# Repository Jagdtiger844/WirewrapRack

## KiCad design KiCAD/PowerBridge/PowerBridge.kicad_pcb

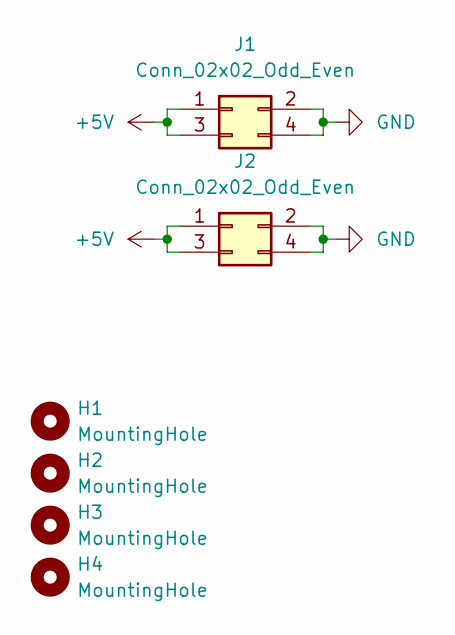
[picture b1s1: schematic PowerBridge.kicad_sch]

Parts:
H1, H2, H3, H4: MountingHole; MountingHole_2.2mm_M2
J1, J2: Conn_02x02_Odd_Even; PinSocket_2x02_P2.54mm_Vertical

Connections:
+5V: J1.1, J1.3, J2.1, J2.3
GND: J1.2, J1.4, J2.2, J2.4

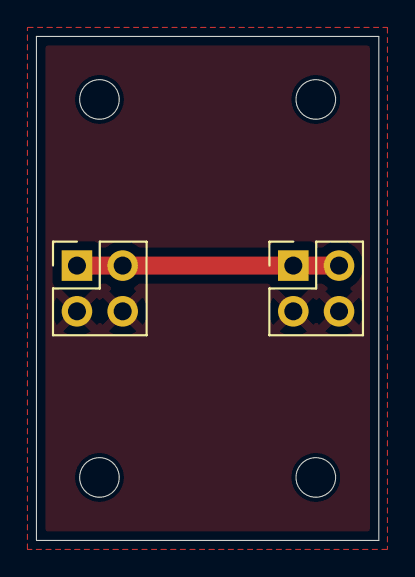
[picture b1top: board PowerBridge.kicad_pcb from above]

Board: 2 copper layers, 19.0 x 28.0 mm, 6 parts (0 on the bottom side), 2 nets.

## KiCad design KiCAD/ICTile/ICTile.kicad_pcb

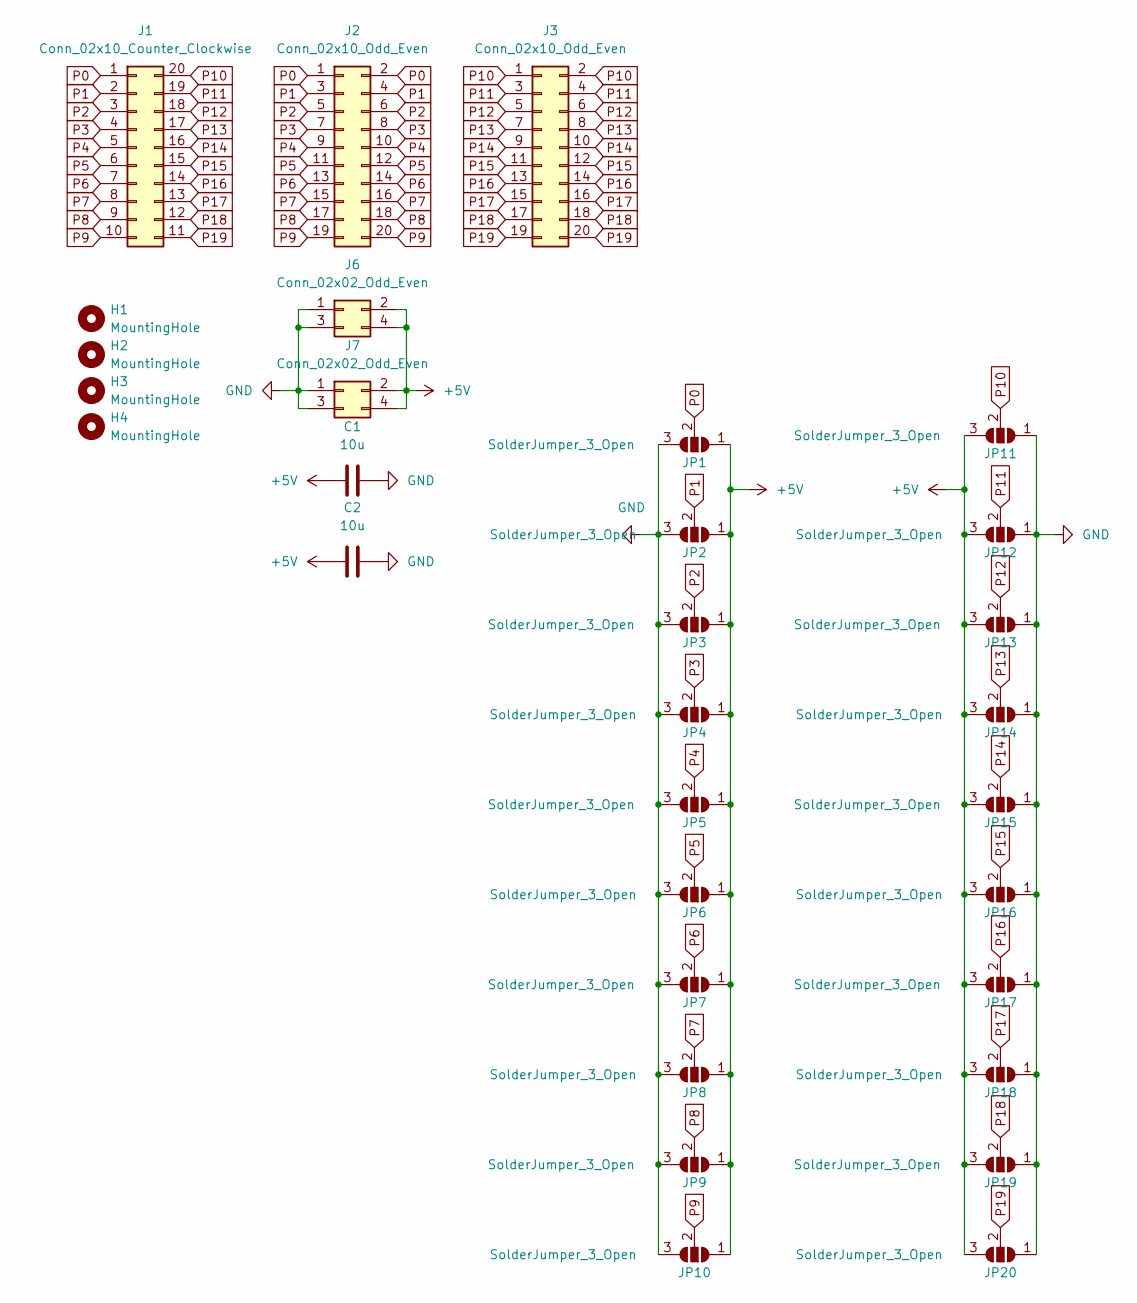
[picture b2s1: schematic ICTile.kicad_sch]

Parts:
C1, C2: 10u; C_1206_3216Metric_Pad1.33x1.80mm_HandSolder
H1, H2, H3, H4: MountingHole; MountingHole_2.2mm_M2
J1: Conn_02x10_Counter_Clockwise; DIP-20_W8.89mm_SMDSocket_LongPads
J2, J3: Conn_02x10_Odd_Even; PinHeader_2x10_P2.54mm_Vertical_SMD
J6, J7: Conn_02x02_Odd_Even; PinHeader_2x02_P2.54mm_Vertical_SMD
JP1, JP2, JP3, JP4, JP5, JP6, JP7, JP8, JP9, JP10, JP11, JP12, JP13, JP14, JP15, JP16, JP17, JP18, JP19, JP20: SolderJumper_3_Open; 1206_3Way_Open

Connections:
+5V: C1.1, C2.1, J6.2, J6.4, J7.2, J7.4, JP1.1 (A), JP2.1 (A), JP3.1 (A), JP4.1 (A), JP5.1 (A), JP6.1 (A), JP7.1 (A), JP8.1 (A), JP9.1 (A), JP10.1 (A), JP11.3 (B), JP12.3 (B), JP13.3 (B), JP14.3 (B), JP15.3 (B), JP16.3 (B), JP17.3 (B), JP18.3 (B), JP19.3 (B), JP20.3 (B)
GND: C1.2, C2.2, J6.1, J6.3, J7.1, J7.3, JP1.3 (B), JP2.3 (B), JP3.3 (B), JP4.3 (B), JP5.3 (B), JP6.3 (B), JP7.3 (B), JP8.3 (B), JP9.3 (B), JP10.3 (B), JP11.1 (A), JP12.1 (A), JP13.1 (A), JP14.1 (A), JP15.1 (A), JP16.1 (A), JP17.1 (A), JP18.1 (A), JP19.1 (A), JP20.1 (A)
P0: J1.1, J2.1, J2.2, JP1.2 (C)
P1: J1.2, J2.3, J2.4, JP2.2 (C)
P2: J1.3, J2.5, J2.6, JP3.2 (C)
P3: J1.4, J2.7, J2.8, JP4.2 (C)
P4: J1.5, J2.9, J2.10, JP5.2 (C)
P5: J1.6, J2.11, J2.12, JP6.2 (C)
P6: J1.7, J2.13, J2.14, JP7.2 (C)
P7: J1.8, J2.15, J2.16, JP8.2 (C)
P8: J1.9, J2.17, J2.18, JP9.2 (C)
P9: J1.10, J2.19, J2.20, JP10.2 (C)
P10: J1.20, J3.1, J3.2, JP11.2 (C)
P11: J1.19, J3.3, J3.4, JP12.2 (C)
P12: J1.18, J3.5, J3.6, JP13.2 (C)
P13: J1.17, J3.7, J3.8, JP14.2 (C)
P14: J1.16, J3.9, J3.10, JP15.2 (C)
P15: J1.15, J3.11, J3.12, JP16.2 (C)
P16: J1.14, J3.13, J3.14, JP17.2 (C)
P17: J1.13, J3.15, J3.16, JP18.2 (C)
P18: J1.12, J3.17, J3.18, JP19.2 (C)
P19: J1.11, J3.19, J3.20, JP20.2 (C)

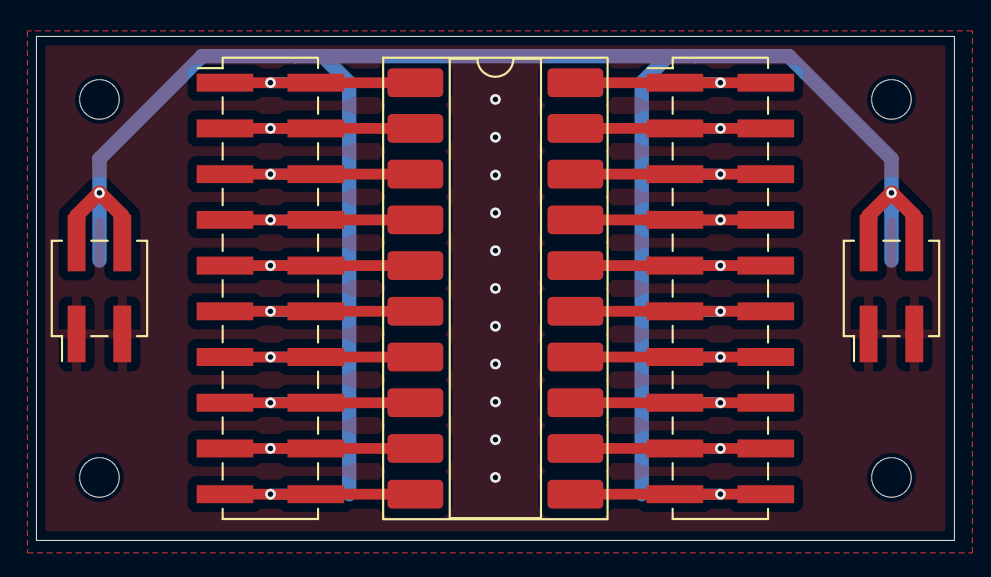
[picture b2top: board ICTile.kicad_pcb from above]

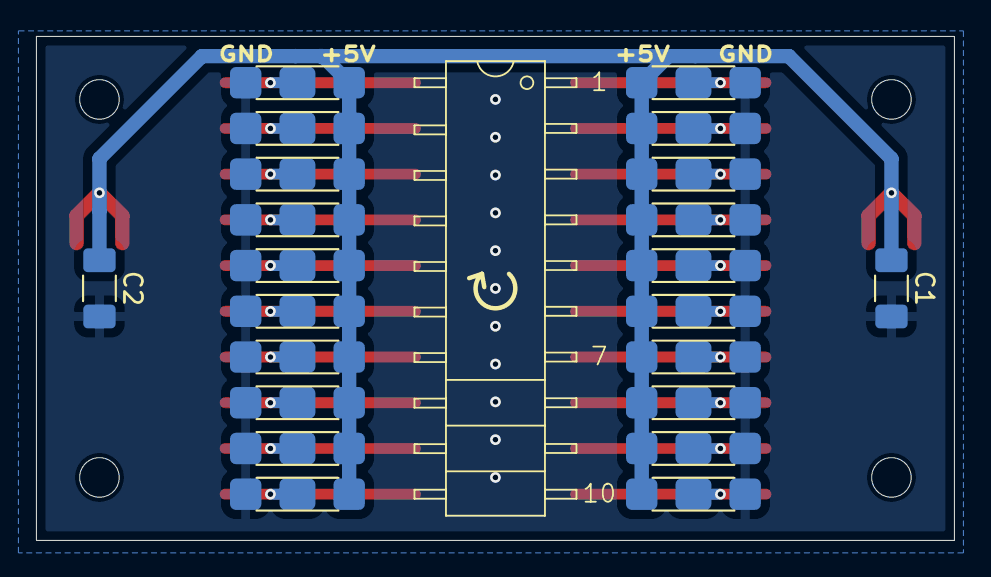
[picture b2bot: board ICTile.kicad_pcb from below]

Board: 2 copper layers, 51.0 x 28.0 mm, 31 parts (22 on the bottom side), 22 nets.

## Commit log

2026-05-10 Initial TileFrame Files
2026-05-13 Redesign to use 0 Ohm Resistor Jumpers instead of Pin Header Jumpers
2026-05-14 Initial Power Bridge Design.
